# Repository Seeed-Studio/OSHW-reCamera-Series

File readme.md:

# Seeed Studio reCamera Hardware

English | [简体中文](README-CN.md)

This repository is the hardware documentation and design-resource hub for the
Seeed Studio reCamera product matrix:

- **reCamera 2002 / 2002w** (SG2002), a modular platform.
- **reCamera Pro** (RV1126B), a higher-performance integrated platform.

reCamera 2002 / 2002w and reCamera Pro are concurrently sold product families
for different application and performance requirements. This repository does
not describe them as replacement generations.

## Product matrix

| | reCamera 2002 / 2002w | reCamera Pro |
| --- | --- | --- |
| Processor | Sophgo SG2002 | Rockchip RV1126B |
| CPU | Dual C906 RISC-V cores | Quad-core Cortex-A53 at 1.2GHz |
| AI acceleration | 1 TOPS INT8 | 3 TOPS NPU |
| Memory | 256MB | 2GB / 4GB LPDDR4 |
| Standard camera | OV5647, 5MP | SC850SL, 8MP, 4K at 30fps |
| Hardware model | Interchangeable core, sensor, and base boards | Integrated camera with expansion interfaces |
| Documentation | [reCamera 2002 hardware](hardware/recamera-2002/) | [reCamera Pro hardware](hardware/recamera-pro/) |

### reCamera 2002 / 2002w

| Standard reCamera 2002 | reCamera 2002 HQ PoE | reCamera Gimbal 2002w |
| --- | --- | --- |
|  |  |  |
| Fixed camera; B101 base | GC2053 sensor; Ethernet and PoE | Two-axis brushless gimbal; B401 CAN base |

The repository contains editable KiCad sources, schematic PDFs, mechanical
files, and revision notes for the C1 core, S-series sensor boards, B-series base
boards, and Gimbal mechanical/power hardware. See the
[reCamera 2002 / 2002w product index](hardware/recamera-2002/products/).

### reCamera Pro

[Buy reCamera Pro 2GB from Seeed Studio](https://www.seeedstudio.com/reCamera-Pro-2GB.html)

The repository currently provides an official-specification snapshot, polished
storefront product images, and technical interface images for reCamera Pro. Editable Pro PCB and
mechanical source files should be added only when an approved hardware release
is available.

## Repository layout

```text
.
|-- hardware/
|   |-- recamera-2002/       # reCamera 2002 family board and mechanical sources
|   `-- recamera-pro/        # reCamera Pro family specifications and images
|-- docs/                    # Official sources and maintenance policy
|-- .github/workflows/       # Repository administration
|-- CONTRIBUTING.md
`-- LICENSE
```

## Scope

This is a **pure hardware repository**. 
If you need to access software-related repositories, please visit the official website.
[reCamera document](https://wiki.seeedstudio.com/recamera/)Obtain these resources from the Seeed Studio software repository.

Gimbal and HQ PoE are product forms within the reCamera 2002 family. Their
product-specific hardware is documented under `hardware/recamera-2002/products/`
and linked to shared boards.

## Source of truth

Hardware summaries are reviewed against official Seeed Studio product and Wiki
pages. See [docs/OFFICIAL_SOURCES.md](docs/OFFICIAL_SOURCES.md) for the source
list and review date. A currently shipped product page takes precedence over a
repository snapshot when specifications or available configurations change.

Contributions must follow [CONTRIBUTING.md](CONTRIBUTING.md). Unless a file says
otherwise, repository content is provided under the [Apache License 2.0](LICENSE).

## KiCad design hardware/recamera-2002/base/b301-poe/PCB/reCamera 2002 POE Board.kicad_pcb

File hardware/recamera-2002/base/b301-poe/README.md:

# B301 PoE base-board reference design

B301 adds Ethernet data and PoE-powered operation for an SG2002 reCamera. The
files here are an open-hardware **reference design** and must not be assumed to
be electrically or mechanically identical to every shipped reCamera HQ PoE
revision.

Editable KiCad sources are in [PCB](PCB/), enclosure files are in
[3D_Printed_Case](3D_Printed_Case/), and design images are in [static](static/).

> [!CAUTION]
> PoE input design involves safety, thermal, isolation, surge, and compliance
> requirements. Review the actual PSE/PD class, component ratings, isolation
> boundaries, heat dissipation, and IEEE 802.3 requirements before building.
> The powered reCamera endpoint is the **PD**; do not describe it as a PSE.

For a commercial reCamera HQ PoE product, follow its dedicated
[official quick-start guide](https://wiki.seeedstudio.com/recamera_hq_poe_getting_started/).

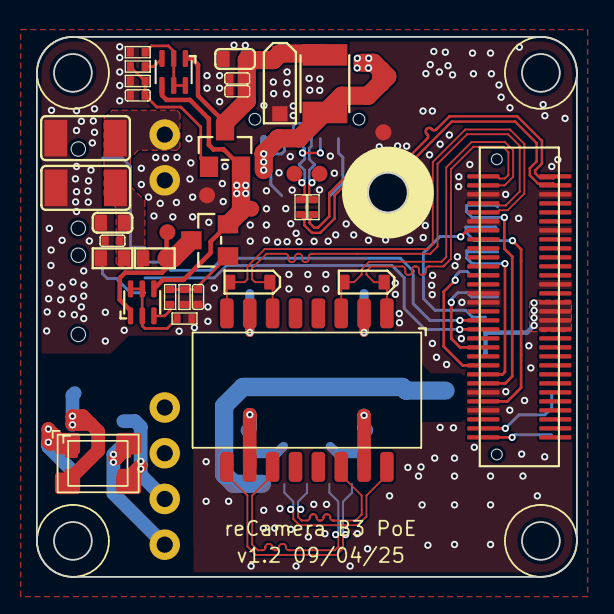
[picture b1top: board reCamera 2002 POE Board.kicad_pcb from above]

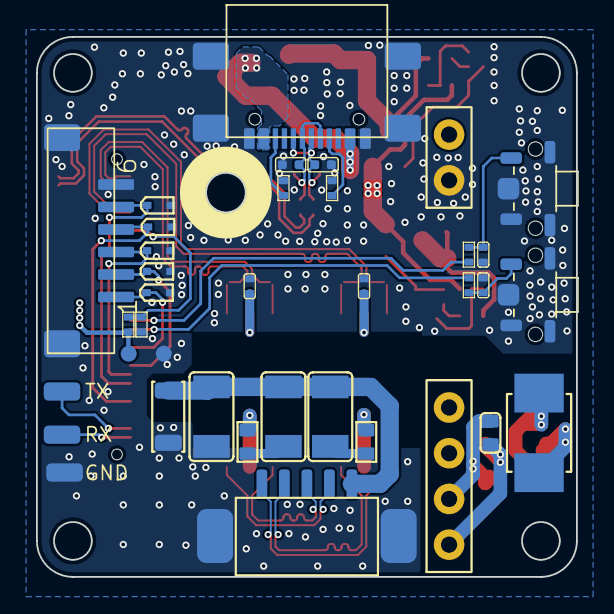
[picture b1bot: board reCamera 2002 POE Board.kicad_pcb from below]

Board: 4 copper layers, 30.0 x 30.0 mm, 75 parts (37 on the bottom side), 47 nets.

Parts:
C2: 100uF; C1206
C3, C4, C7, C13: 100nF; C0402
C5, C10, C17: 1nF; C1206
C6, C16: 10uF; C0603
C9, C18: 10pF; C0402
C11: 100pF; C0402
C12: 47uF; C1206
C19: 10nF; C0603
C49, C50: 10nF; C0402
D1: SMF5.0CA; SOD-123
D2, D3: ESDPSA0402V05; ESD-0402
D4: 58V 600W; DO-214AA-SMB-NONPOLAR
D5, D6, D7, D8, D13: CESD3V3D5; SOD-523
D11, D12: UDD32C03L01; SOD-323
F1: 2A; F1210
FB1: 120R; L0603
J1: ST-BTB-058060-A; BTB60-Male-Female-0.5-17.7x4.4mm
J2: ST-FH-254-0106-1*2P-PC3.0; JST2P-2.54-5.58X2.5X3.5MM
J3: 1.25-5A-WT; JST5_2P_1d25_7_9x4_3x3_4mm
J4: ST-FH-254-0106-1*4P-PC3.0; JST4P-2.54-10.66X2.5X3.5MM
J5: 1.25-6A-LT; FPC6-1.25-12.5X3.7X4.65MM
K1, K2: TD-1100AP-A4N-D1R; SW5-SMD-4.56X2.3X1.9MM
L1: CMC4532H-102-2P-T; INT4-2.2-4.5X3.2X2.8MM
L3: 300mA; INT4-1.45-3.3X2.5X2.5MM
Q1, Q2: CJ3407; SOT23
R2, R34, R39, R40: 100K; R0402
R4: 10K; R0402
R5: 20K; R0402
R6: 1M; R1206
R7, R12: 5.1K; R0402
R8, R9, R16, R17: 0R; R0402
R13, R14: 75R; R0603
R18: 1K; R0603
R41, R43: 100R; R0402
T1: KHX1631SR; TRF_16p_1d27_12d7x7d15x5d1mm
TP1, TP2, TP3: Test Point; TP-80X40MIL
TP4, TP5, TP6, TP8, TP9, TP10, TP11, TP12, TP15: Test Point; TP-D35MIL
U9, U10: BC856S; SOT-363
USB1: ST-USB-Y3120; USB2.0-TYPE-C-SMD-12X7.35X3.3MM

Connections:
+5V: F1.2, TP8.1 (T), USB1.A4_B9 (A4/B9/VBUS), USB1.B4_A9 (B4/A9/VBUS)
/POE Board/DN: D2.1, R9.1, TP4.1 (T), USB1.A7 (A7/DN1), USB1.B7 (B7/DN2)
/POE Board/DP: D3.1, R8.1, TP5.1 (T), USB1.A6 (A6/DP1), USB1.B6 (B6/DP2)
/POE Board/PHYRXN: J3.1, T1.9
/POE Board/PHYRXP: J3.2, T1.11
/POE Board/PHYTXN: J3.3, T1.14
/POE Board/PHYTXP: J3.4, T1.16
/POE Board/POE_VIN+_ModeA: D4.2, L1.1, L3.1, R14.2, T1.15
/POE Board/POE_VIN-_ModeA: D4.1, L1.4, L3.2, R13.2, T1.10
DEBUG_UART0_RX: J1.60, TP2.1 (T)
DEBUG_UART0_TX: J1.58, TP1.1 (T)
EPHY_RXN: D12.1, J1.10, T1.8
EPHY_RXP: D12.2, J1.8, T1.6
EPHY_TXN: D11.1, J1.4, T1.3
EPHY_TXP: D11.2, J1.2, T1.1
GND: C2.2, C3.1, C4.1, C6.2, C7.2, C9.2, C10.1, C11.2, C12.2, C13.2, C16.2, C18.2, C49.2, C50.2, D1.1, D2.2, D3.2, D5.1 (+), D6.1 (+), D7.1 (+), D8.1 (+), D13.1 (+), J1.5, J1.6, J1.12, J1.13, J1.25, J1.28, J1.30, J1.50, J1.54, J2.1, J3.6, J3.7, J5.6, J5.7, J5.8, K1.2, K1.S1, K1.S2, K1.S3, K2.2, K2.S1, K2.S2, K2.S3, R2.1, R4.1, R6.2, R7.1, R12.2, R18.1, R34.1, R39.1, R40.1, TP3.1 (T), TP6.1 (T), TP11.1 (T), TP12.1 (T), USB1.A1_B12 (A1/B12/GND), USB1.B1_A12 (B1/A12/GND), USB1.S1, USB1.S2, USB1.S3, USB1.S4
GNDPWR: C5.2, C10.2, C17.2, J3.5, R6.1
unnamed: C3.2, T1.2
unnamed: C4.2, T1.7
unnamed: C5.1, R13.1
unnamed: C9.1, K2.1, R16.2
unnamed: C2.1, C12.1, C13.1, C16.1, FB1.2, J2.2, R18.2
unnamed: C17.1, R14.1
unnamed: C18.1, K1.1, R17.2
unnamed: C19.1, J4.1, L1.2, L3.4
unnamed: C19.2, J4.2, L1.3, L3.3
unnamed: C50.1, Q1.1 (G), R39.2, R43.1
unnamed: C49.1, Q2.1 (G), R2.2, R41.1
unnamed: R34.2, U9.2, U9.5, U9.6
unnamed: R40.2, U10.2, U10.5, U10.6
unnamed: R41.2, U9.3
unnamed: R43.2, U10.3
unnamed: R12.1, USB1.A5 (A5/CC1)
unnamed: R7.2, USB1.B5 (B5/CC2)
POE_VOUT_5V: FB1.1, Q2.3 (D), TP10.1 (T), U9.1
SDIO_CLK/3V3: D5.2 (-), J1.52, J5.4
SDIO_CMD/3V3: D13.2 (-), J1.48, J5.5
SDIO_D0/3V3: D6.2 (-), J1.46, J5.3
SDIO_D1/3V3: D7.2 (-), J1.44, J5.2
SDIO_D3/3V3: D8.2 (-), J1.40, J5.1
UPGRAD_KEY: J1.36, R16.1
USB_DET: J1.14, R4.2, R5.1
USB_DN: J1.1, R9.2
USB_DP: J1.3, R8.2
VIN: J1.29, J1.31, J1.33, J1.35, Q1.2 (S), Q2.2 (S), R5.2, TP9.1 (T), TP15.1 (T), U9.4, U10.4
VIN_5V: C6.1, C7.1, C11.1, D1.2, F1.1, Q1.3 (D), U10.1
nRESET: J1.34, R17.1

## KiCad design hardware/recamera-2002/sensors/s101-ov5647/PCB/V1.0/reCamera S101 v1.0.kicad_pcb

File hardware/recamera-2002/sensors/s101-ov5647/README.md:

# S101 OV5647 sensor board

S101 is the default sensor board shipped with standard reCamera 2002/2002w
Basic products.

| Item | Value |
| --- | --- |
| Sensor | OV5647, rolling shutter |
| Resolution | 5MP (2592 × 1944) |
| Optical format | 1/4 inch |
| Pixel size | 1.4µm |
| Aperture | F2.8 |
| Focal length | 3.46mm |
| Field of view | 65° |
| Output | RAW10 |

The board also carries the reCamera's microphone, external-speaker connection,
four fill LEDs, and status/programmable LEDs.

## Resources

- Editable KiCad sources: [PCB](PCB/)
- [Schematic PDF](static/reCamera%20S101%20v1.1_SCH_PDF_240927.pdf)
- Enclosure files: [3D_Printed_Case](3D_Printed_Case/)

The repository includes more than one PCB revision. Use the revision matching
the physical board and validate it before manufacture.

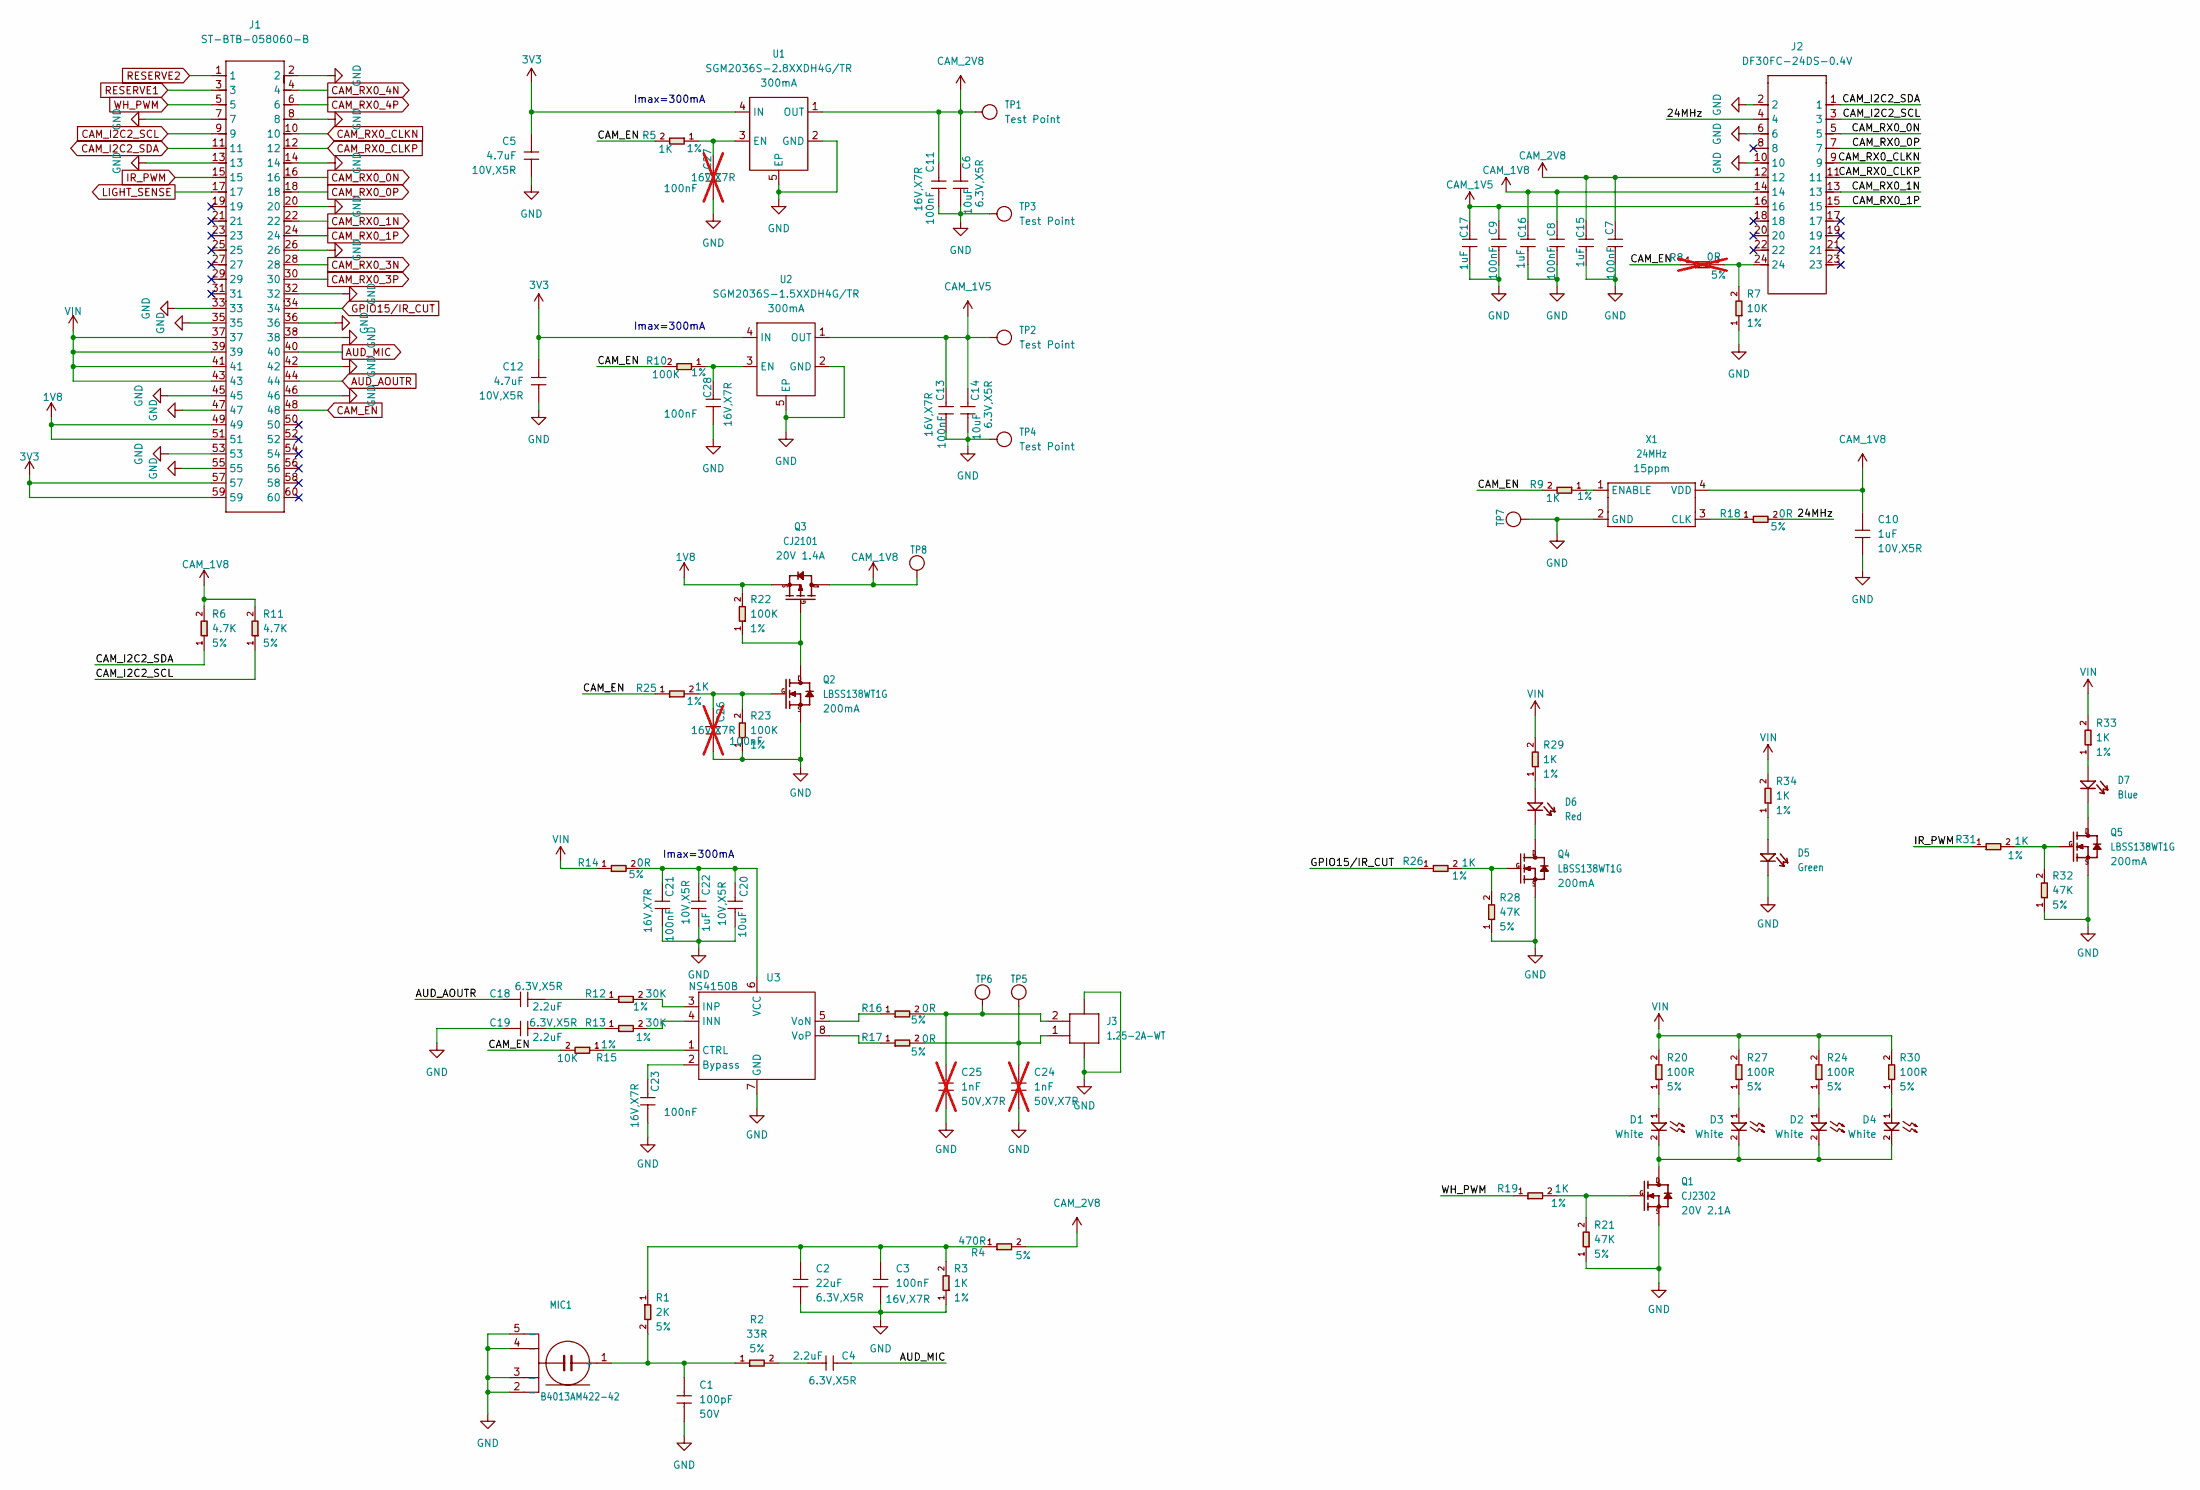
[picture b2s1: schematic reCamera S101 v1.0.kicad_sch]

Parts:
C1: 100pF; C0402; Voltage Rating 50V; MPN CC0402JRNPO9BN101
C2: 22uF; C0603; Voltage Rating 6.3V,X5R; MPN CC0603MRX5R5BB226
C3, C7, C8, C9, C11, C13, C21, C23, C28: 100nF; C0402; Voltage Rating 16V,X7R; MPN CC0402KRX7R7BB104
C4, C18, C19: 2.2uF; C0402; Voltage Rating 6.3V,X5R; MPN CC0402MRX5R5BB225
C5, C12: 4.7uF; C0603; Voltage Rating 10V,X5R; MPN CC0603KRX5R6BB475
C6, C14: 10uF; C0402; Voltage Rating 6.3V,X5R; MPN CC0402MRX5R5BB106
C10, C15, C16, C17, C22: 1uF; C0402; Voltage Rating 10V,X5R; MPN CC0402KRX5R6BB105
C20: 10uF; C0603; Voltage Rating 10V,X5R; MPN CC0603KRX5R6BB106
C24, C25: 1nF; C0402; Voltage Rating 50V,X7R; MPN CC0402KRX7R9BB102; not fitted
C26, C27: 100nF; C0402; Voltage Rating 16V,X7R; MPN CC0402KRX7R7BB104; not fitted
D1, D2, D3, D4: White; LED2-2.54-4.15MM; MPN 204-15UTC/S400-X9
D5: Green; LED-0402; MPN BL-HGE37A-AV-TRB
D6: Red; LED-0402; MPN BL-HUB37A-AV-TRB
D7: Blue; LED-0402; MPN BL-HB337A-AV-TRB
J1: ST-BTB-058060-B; BTB60-Male-Female-0.5-17.7x4.4mm; MPN ST-BTB-058060-B
J2: DF30FC-24DS-0.4V; BTB2x12P_0d4_7_02x3_76x0_9mm; MPN DF30FC-24DS-0.4V
J3: 1.25-2A-WT; GH2-1.25-7.4X5.3X3.5MM; MPN 1.25-2A-WT
MIC1: B4013AM422-42; MIC-5P-SMD-4X4MM; MPN B4013AM422-42
Q1: CJ2302; SOT23; Rating 20V 2.1A; MPN CJ2302
Q2, Q4, Q5: LBSS138WT1G; SOT-323; Rating 200mA; MPN LBSS138WT1G
Q3: CJ2101; SOT-323; Rating 20V 1.4A; MPN CJ2101
R1: 2K; R0402; Power Rating 5%; MPN RC0402JR-072KL
R2: 33R; R0402; Power Rating 5%; MPN RC0402JR-0733RL
R3, R5, R9, R19, R25, R26, R29, R31, R33, R34: 1K; R0402; Power Rating 1%; MPN RC0402FR-071KL
R4: 470R; R0402; Power Rating 5%; MPN RC0402JR-07470RL
R6, R11: 4.7K; R0402; Power Rating 5%; MPN RC0402JR-074K7L
R7, R15: 10K; R0402; Power Rating 1%; MPN RC0402FR-0710KL
R8: 0R; R0402; Power Rating 5%; MPN RC0402JR-070RL; not fitted
R10, R22, R23: 100K; R0402; Power Rating 1%; MPN RC0402FR-07100KL
R12, R13: 30K; R0402; Power Rating 1%; MPN RC0402FR-0730KL
R14, R16, R17, R18: 0R; R0402; Power Rating 5%; MPN RC0402JR-070RL
R20, R24, R27, R30: 100R; R0603; Power Rating 5%; MPN RC0603JR-07100RL
R21, R28, R32: 47K; R0402; Power Rating 5%; MPN RC0402JR-0747KL
TP1, TP2, TP3, TP4, TP5, TP6, TP7, TP8: Test Point; TP-D35MIL; Part Type Test Point
U1: SGM2036S-2.8XXDH4G/TR; X2SON4-0.625-1x1x0.6mm; Rating 300mA; MPN SGM2036S-2.8XXDH4G/TR
U2: SGM2036S-1.5XXDH4G/TR; X2SON4-0.625-1x1x0.6mm; Rating 300mA; MPN SGM2036S-1.5XXDH4G/TR
U3: NS4150B; MSOP8-0.65-3X3X1MM; MPN NS4150B
X1: 24MHz; X4-SMD-2.0X1.6MM; Rating 15ppm; MPN 9C24000004

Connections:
1V8: J1.49, J1.51, Q3.2 (S), R22.2
3V3: C5.1, C12.1, J1.57, J1.59, U1.4 (IN), U2.4 (IN)
/24MHz: J2.4, R18.2
AUD_AOUTR: C18.1, J1.44
AUD_MIC: C4.1, J1.40
CAM_1V5: C9.1, C13.1, C14.1, C17.1, J2.16, TP2.1 (T), U2.1 (OUT)
CAM_1V8: C8.1, C10.1, C16.1, J2.14, Q3.3 (D), R6.2, R11.2, TP8.1 (T), X1.4 (VDD)
CAM_2V8: C6.1, C7.1, C11.1, C15.1, J2.12, R4.2, TP1.1 (T), U1.1 (OUT)
CAM_EN: J1.48, R5.2, R8.1, R9.2, R10.2, R15.2, R25.1
CAM_I2C2_SCL: J1.9, J2.3, R11.1
CAM_I2C2_SDA: J1.11, J2.1, R6.1
CAM_RX0_0N: J1.16, J2.5
CAM_RX0_0P: J1.18, J2.7
CAM_RX0_1N: J1.22, J2.13
CAM_RX0_1P: J1.24, J2.15
CAM_RX0_3N: J1.28
CAM_RX0_3P: J1.30
CAM_RX0_4N: J1.4
CAM_RX0_4P: J1.6
CAM_RX0_CLKN: J1.10, J2.9
CAM_RX0_CLKP: J1.12, J2.11
GND: C1.2, C2.2, C3.2, C5.2, C6.2, C7.2, C8.2, C9.2, C10.2, C11.2, C12.2, C13.2, C14.2, C15.2, C16.2, C17.2, C19.1, C20.2, C21.2, C22.2, C23.2, C24.2, C25.2, C26.2, C27.2, C28.2, D5.2 (-), J1.2, J1.7, J1.8, J1.13, J1.14, J1.20, J1.26, J1.32, J1.33, J1.35, J1.36, J1.38, J1.42, J1.45, J1.46, J1.47, J1.53, J1.55, J2.2, J2.6, J2.10, J3.3, J3.4, MIC1.2 (-), MIC1.3 (-), MIC1.4 (-), MIC1.5 (-), Q1.2 (S), Q2.2 (S), Q4.2 (S), Q5.2 (S), R3.1, R7.1, R21.1, R23.1, R28.1, R32.1, TP3.1 (T), TP4.1 (T), TP7.1 (T), U1.2 (GND), U1.5 (EP), U2.2 (GND), U2.5 (EP), U3.7 (GND), X1.2 (GND)
GPIO15/IR_CUT: J1.34, R26.1
IR_PWM: J1.15, R31.1
LIGHT_SENSE: J1.17
unnamed: C2.1, C3.1, R1.1, R3.2, R4.1
unnamed: C4.2, R2.2
unnamed: C18.2, R12.1
unnamed: C19.2, R13.1
unnamed: D1.1, R20.1
unnamed: D2.1, R24.1
unnamed: D3.1, R27.1
unnamed: D4.1, R30.1
unnamed: D5.1 (+), R34.1
unnamed: D6.1 (+), R29.1
unnamed: D6.2 (-), Q4.3 (D)
unnamed: D7.1 (+), R33.1
unnamed: D7.2 (-), Q5.3 (D)
unnamed: J2.24, R7.2, R8.2
unnamed: C1.1, MIC1.1 (+), R1.2, R2.1
unnamed: D1.2, D2.2, D3.2, D4.2, Q1.3 (D)
unnamed: Q1.1 (G), R19.2, R21.2
unnamed: Q2.3 (D), Q3.1 (G), R22.1
unnamed: C26.1, Q2.1 (G), R23.2, R25.2
unnamed: Q4.1 (G), R26.2, R28.2
unnamed: Q5.1 (G), R31.2, R32.2
unnamed: C24.1, J3.1, R17.2, TP5.1 (T)
unnamed: C25.1, J3.2, R16.2, TP6.1 (T)
unnamed: C27.1, R5.1, U1.3 (EN)
unnamed: C28.1, R10.1, U2.3 (EN)
unnamed: C23.1, U3.2 (Bypass)
unnamed: R15.1, U3.1 (CTRL)
unnamed: R13.2, U3.4 (INN)
unnamed: R12.2, U3.3 (INP)
unnamed: C20.1, C21.1, C22.1, R14.2, U3.6 (VCC)
unnamed: R16.1, U3.5 (VoN)
unnamed: R17.1, U3.8 (VoP)
unnamed: R18.1, X1.3 (CLK)
unnamed: R9.1, X1.1 (ENABLE)
RESERVE1: J1.3
RESERVE2: J1.1
VIN: J1.37, J1.39, J1.41, J1.43, R14.1, R20.2, R24.2, R27.2, R29.2, R30.2, R33.2, R34.2
WH_PWM: J1.5, R19.1

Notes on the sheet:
Imax=300mA

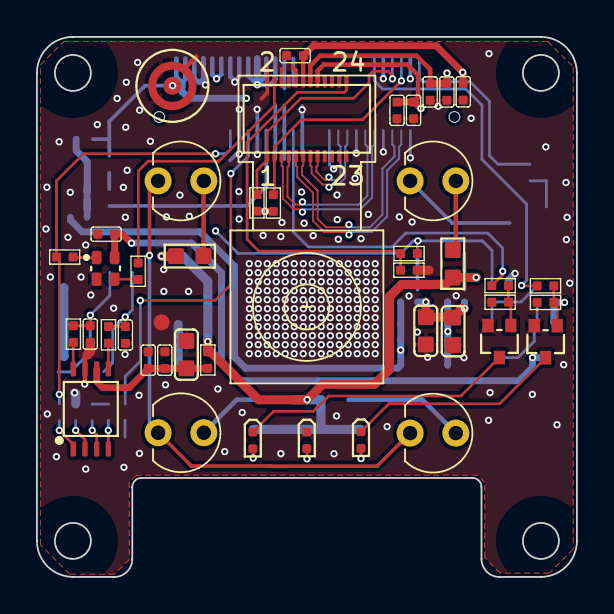
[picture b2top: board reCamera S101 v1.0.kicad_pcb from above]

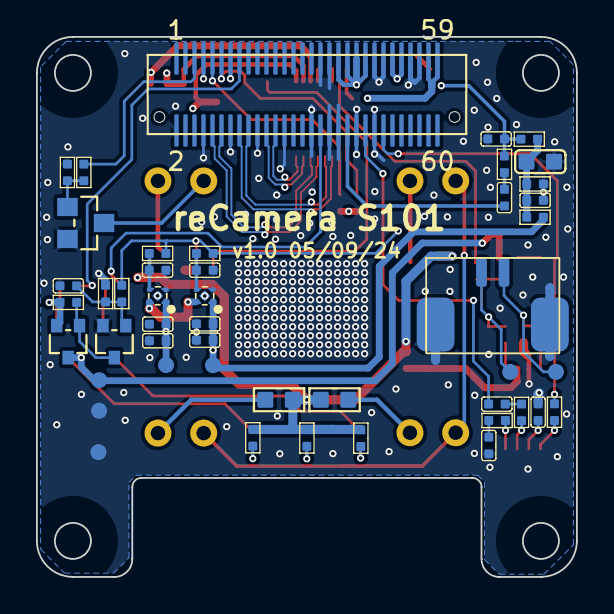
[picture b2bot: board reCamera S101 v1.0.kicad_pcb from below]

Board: 4 copper layers, 30.0 x 30.0 mm, 90 parts (47 on the bottom side), 56 nets.

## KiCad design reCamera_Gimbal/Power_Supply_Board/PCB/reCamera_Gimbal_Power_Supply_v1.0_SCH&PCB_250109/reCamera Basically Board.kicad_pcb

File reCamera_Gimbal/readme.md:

# 🎨 reCamera Gimbal Programmable Development Kit 

## 🔥Introduction
Welcome to the reCamera Gimbal Programmable Development Kit. This kit provides resources and tools for developers to control and customize the reCamera Gimbal. It includes sample code for debugging gimbal motor operations and status outputs, offering program entry points to drive the gimbal motor using CAN for precise control and functionality.

## Table of Contents

- [🔩 Pre-requisite](#-pre-requisite)
- [🪢 Gimbal Dashboard Preview with Node-RED ](#-gimbal-dashboard-preview-with-node-red)
- [⚙️ Hardware Overview](#-hardware-overview)
- [💡 Custom Development](#-custom-development)
- [🔥 Gimbal STP](#-gimbal-stp)
- [📀 Flash motors firmware](#-flash-motors-firmware)

## 🔩 Pre-requisite
- reCamera OS 0.2.0
- 12V 2A power supply
- USB Type-C cable

## 🪢 Gimbal Dashboard Preview with Node-RED

Gimbal Node-REd Dashboard includes camera preview, model confidence/IoU Settings, gimbal manual control, object auto-tracking and shortcut buttons such as sleep, standby, calibration and Emergency Stop. The PID settings are also included for fine-tuning as each device is self-assembled.

You can see how to deploy json flow on Node-RED [here](https://github.com/jby5122/OSHW-reCamera-Series/tree/main/Node-RED_Flow#%EF%B8%8F-how-to-deploy-dashboard-flow). 

- View [Gimbal Dashboard V1.0.json](./src/Dashboard/Gimbal_DashboardV1.0.json) (PID settings are also included)
- View [Motor_PID_Config.json](./src/Dashboard/Motor_PID_Config.json) (Individual PID settings for each motor in case you want to add this to your own flow)

## Hardware Overview

To enable the reCamera to drive the gimbal motor, the reCamera's base board needs to be replaced to [B4_CAN](https://github.com/Seeed-Studio/OSHW-reCamera-Series/tree/main/reCamera_Base_Board/B4_CAN) to enable CAN communication.

Up             |  Bottom
:-------------------------:|:-------------------------:
  |  

You can use the Debugging Port connections to control the motor and communicate with the reCamera via the upper monitor. Alternatively, you can control the motor directly through the reCamera.

| **Processing System**                |                                                         |                                                         |
| ------------------------------------ | ------------------------------------------------------- | ------------------------------------------------------- |
| SOC                                  | SG2002                                                  |                                                         |
| CPU                                  | C906@1GHZ + C906@700MHz                                 |                                                         |
| AI Performance                       | 1 Tops @ Int8                                           |                                                         |
| MCU                                  | 8051 @ 8KB SRAM                                         |                                                         |
| Operating System                     | Linux                                                   |                                                         |
| Memory                               | 256 MB                                                  |                                                         |
| Video Encoder                        | 5MP @ 30Fps                                             |                                                         |
| **Basic**                            |                                                         |                                                         |
| Camera Sensor                        | OV5647                                                  |                                                         |
| eMMC                                 | 8GB / 64GB                                              |                                                         |
| Power Supply                         | 12-24V DC Jack to XT30 connector                        |                                                         |
| Power Consumption(static)            | 12V,185mA; 24V,150mA                                    |                                                         |
| **Interface**                        |                                                         |                                                         |
| USB                                  | USB 2.0 Type-C                                          |                                                         |
| Wireless                             | Wi-Fi 2.4G/5G Bluetooth 4.2/5.0                         |                                                         |
| Button                               | 1 x Reboot Button, 1 x User Button                      |                                                         |
| Fill LEDs                            | 4 x 0.3w White Light                                    |                                                         |
| LED                                  | 1 x Power Indicator, 2 x IO programmable indicator      |                                                         |
| Mic                                  | On-Board Mic                                            |                                                         |
| Speaker                              | External Speaker                                        |                                                         |
| **Motor Spec**                       | MS3008                                                  | MS3506                                                  |
| Turns                                | 54                                                      | 60                                                      |
| Rated Voltage(V)                     | 12                                                      | 12                                                      |
| Max Speed(rpm)                       | 2000                                                    | 2100                                                    |
| Rated Torque(N.m)                    | 0.04                                                    | 0.05                                                    |
| Rated Speed(rpm)                     | 1160                                                    | 1250                                                    |
| Rated Current(A)                     | 0.64                                                    | 0.79                                                    |
| Max Power(W)                         | 4.6                                                     | 6.4                                                     |
| Motor Poles                          | 14                                                      | 14                                                      |
| Operating temperature (℃)            | -25~60                                                  | -25~60                                                  |
| Motor Weight(g)                      | 49                                                      | 63                                                      |
| Drive Input Voltage (V)              | 6~16                                                    | 6~16                                                    |
| Communication                        | CAN                                                     | CAN                                                     |
| Communication Frequency (Hz)         | CAN@1Mbps:2KHz                                          | CAN@1Mbps:2KHz                                          |
| Encoder                              | 15 bit Magnetic Encoder                                 | 15 bit Magnetic Encoder                                 |
| CAN Baut Rate                        | 100K、125K、250K、500K、1M                              | 100K、125K、250K、500K、1M                              |
| Control Mode                         | Open Loop(24KHz) /Speed Loop(4KHz) /Position Loop(2KHz) | Open Loop(24KHz) /Speed Loop(4KHz) /Position Loop(2KHz) |
| **Ambient Conditions**               |                                                         |                                                         |
| Operating Temperature                | -20～50 ℃                                               |                                                         |
| Operating Humidity                   | 0～90%                                                  |                                                         |
| **Others**                           |                                                         |                                                         |
| Heat Dissipation                     | Fanless                                                 |                                                         |
| Warranty                             | 1 years                                                 |                                                         |
| **Mechanical**                       |                                                         |                                                         |
| Finished ProductDimension(W x H x D) | 68x112x71mm                                             |                                                         |
| Enclosure                            | Polyamide(PA) Nylon                                     |                                                         |
| Weight(Net)                          | 230g                                                    |                                                         |

## 💡 Custom Development

First, you need to prepare a linux operating system to compile the program.
To compile a binary that can run on reCamera, [the cross-compiler tool](https://github.com/sophgo/host-tools/tree/bd66fcc8ed918eac4d6ac076ff8b1da7290b66cb) for riscv needs to be downloaded. 

### Cross-Compilation

Open a terminal in any directory on your Ubuntu system.
You can download host-tools by running this command on your linux system:

```bash
sudo apt install vim
sudo apt install git
git clone https://github.com/sophgo/host-tools.git
```

After the download is complete go to the file "/host-tools/gcc/riscv64-linux-musl-x86_64/bin"

Enter "pwd" to see the absolute path and copy it.

```
pwd
```

```
cd
vim .bashrc
```

Based on the previous “pwd” command, add the following to the end of the file 

```
export PATH=$PATH:/home/kong/Downloads/host-tools/gcc/riscv64-linux-musl-x86_64/bin
```

Click esc and type “:wq” to save the .bashrc.

```
source .bashrc
```

Go back to the OSHW-reCamera-Series/reCamera_Gimbal/src/send directory. Compile can_send.c and run it.

```
riscv64-unknown-linux-musl-gcc can_send.c -o can_send
```

Open a terminal in the directory where can_send is stored.

```
scp ./can_send root@192.168.42.1:~/
```

```
ssh root@192.168.42.1
```

```
touch Angle.txt 
./can_send

echo "1_90_90+2_90_90" >> Angle.txt
```

## 🔥 Gimbal STP

You can [download the STP file](./3D_Printed_Case) of this gimbal for 3D printing and assemble it. 

| Preview | Models |
| ------- | ------ |
|  | [Download](./3D_Printed_Case/recamera-yantai_arm_30.stp)       |
|  | [Download](./3D_Printed_Case/platform-box_29.stp)              |
|  | [Download](./3D_Printed_Case/bottom-plate_10.stp)              |
|  | [Download](./3D_Printed_Case/brushlessmotor-ms3506_4.stp)      |
|  | [Download](./3D_Printed_Case/brushlessmotor-ms3008v2_2.stp)    |
|  | [Download](./3D_Printed_Case/recamera-gimbalcover-4040_20.stp) |
|  | [Download](./3D_Printed_Case/can-case_3.stp)                   |
|  | [Download](./3D_Printed_Case/recamera-middleframe-4040-1_27.stp)|
|  | [Download](./3D_Printed_Case/recamera-sensorcover-4040-1_36.stp)|
|  | [Download](./3D_Printed_Case/glass-4040_6.stp)                 |

## 📀 Flash motors firmware

### Motor ID Set

ID changes can be made using MS_Motor/LK motor tool [V2.35.exe](MotorTools/CN/KY%20motor%20tool%20V2.35.exe). Connect the PC (Windows) to the USB-CAN module, with H, L, and GND of the USB-CAN module connected to H, L, and V- of the motor. Connect the positive and negative terminals of a 12V power supply to V+ and V- of the motor to enable parameter changes. For further instructions on using LK motor tool V2.35.exe, refer to MotorTools/EN/Upper_monitor_motor_debuging_instruction.pdf. 

Only two motors are used in this head, so it is sufficient to set the IDs of the two motors to 01 and 02 respectively.

### How to update motor firmware
WIP...

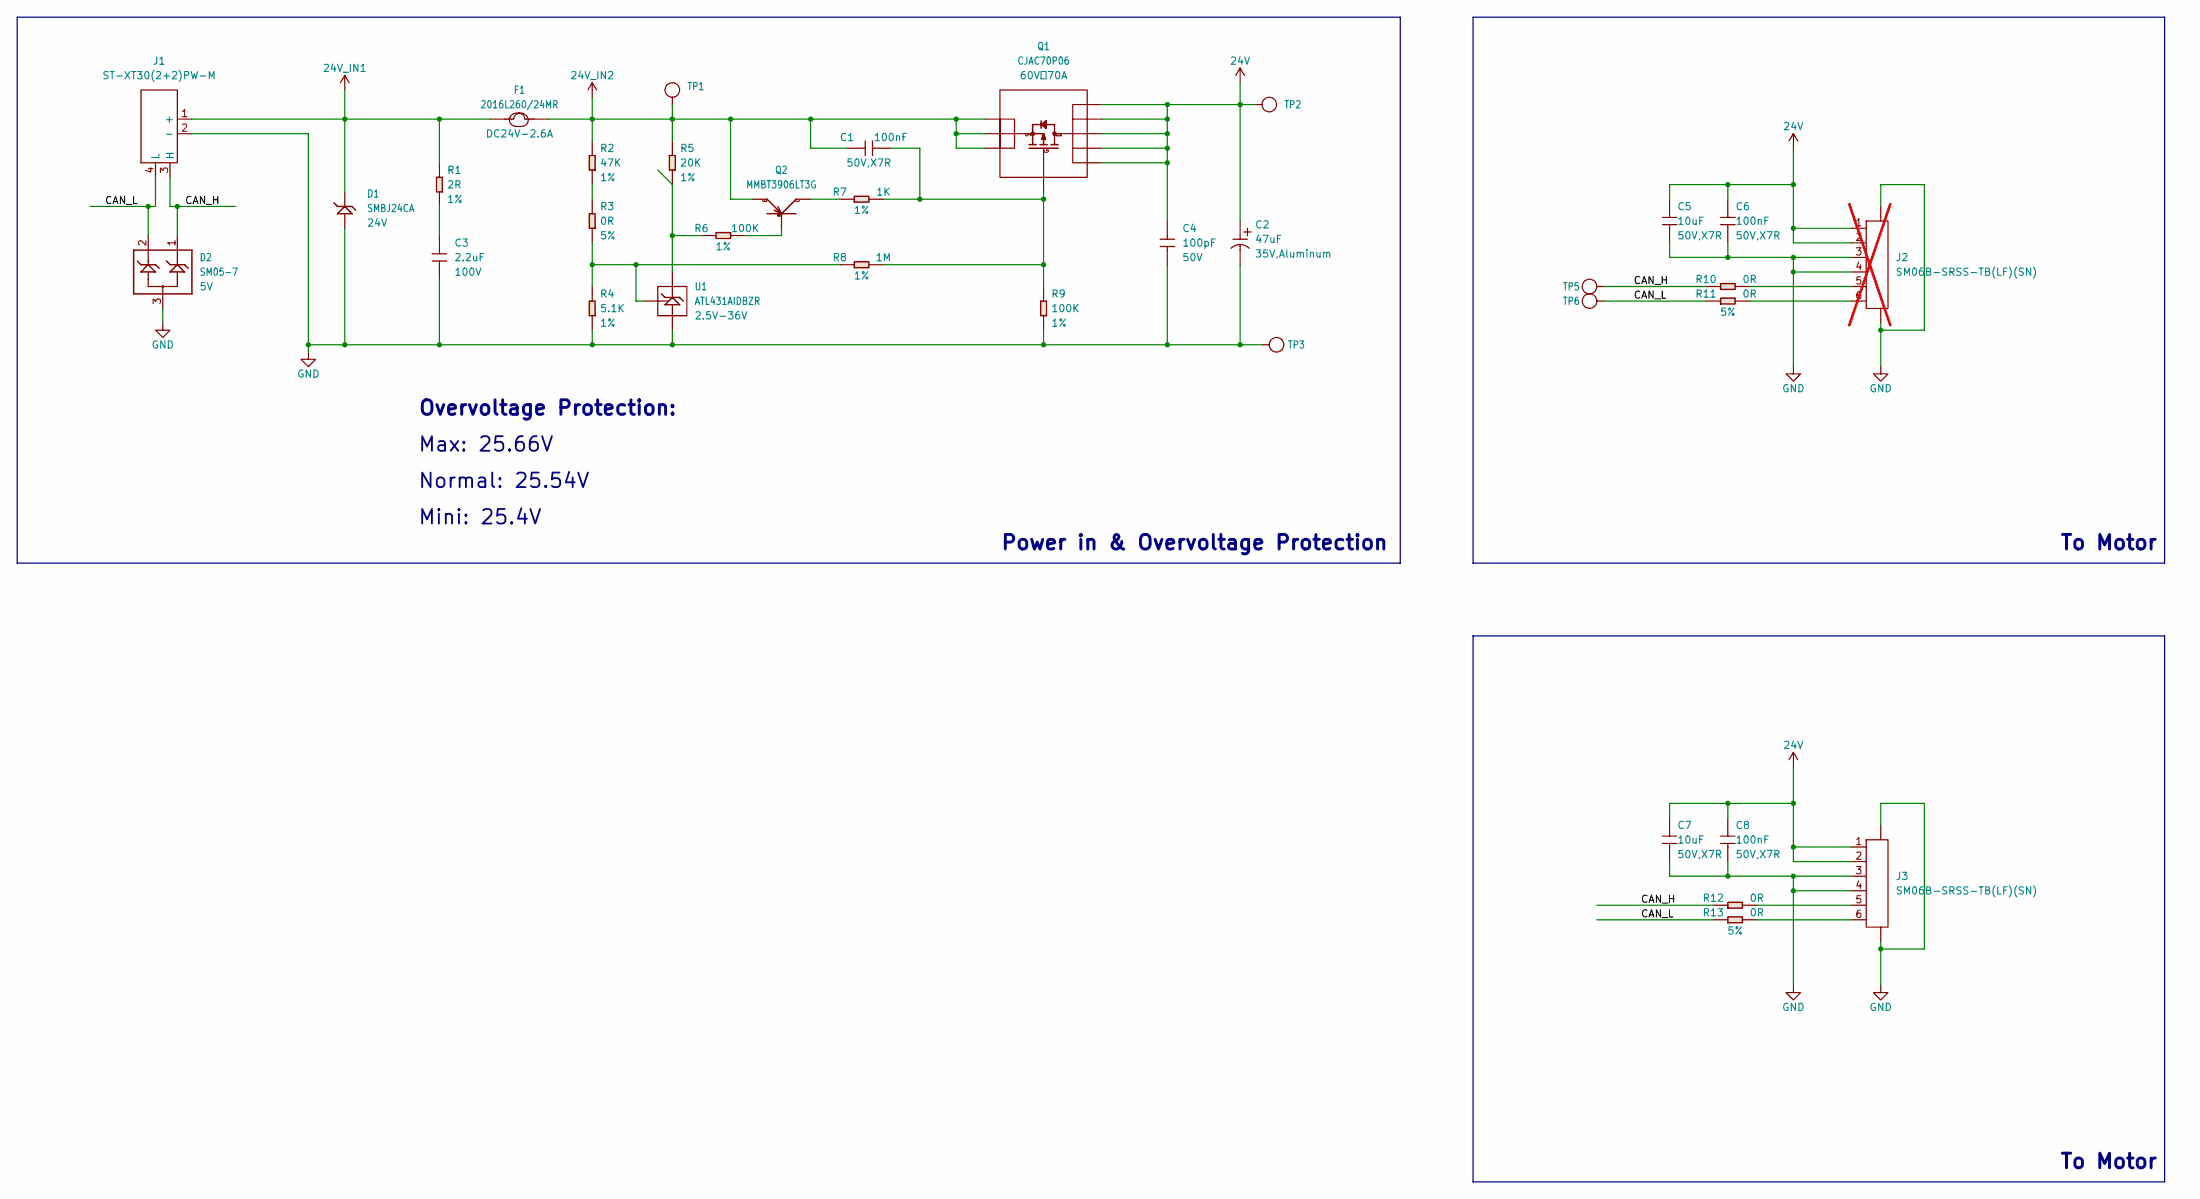
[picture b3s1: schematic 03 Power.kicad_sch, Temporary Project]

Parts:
C1, C6, C8: 100nF; C0603; Voltage Rating 50V,X7R; MPN CC0603KRX7R9BB104
C2: 47uF; ELECTRO-SMD-C-6MM; Voltage Rating 35V,Aluminum; MPN 35TZV47M6.3X6.1
C3: 2.2uF; C1210; Voltage Rating 100V; MPN CC1210KKX7R0BB225
C4: 100pF; C0402; Voltage Rating 50V; MPN CC0402JRNPO9BN101
C5, C7: 10uF; C1206; Voltage Rating 50V,X7R; MPN CL31B106KBHNNNE
D1: SMBJ24CA; DO-214AA_SMB; Rating 24V; MPN SMBJ24CA
D2: SM05-7; SOT-23; Rating 5V; MPN SM05-7
F1: 2016L260/24MR; F2016; Rating DC24V-2.6A; MPN 2016L260/24MR
J1: ST-XT30(2+2)PW-M; XT30-2+2P-15.5x12.5x5.2mm; MPN ST-XT30(2+2)PW-M
J2: SM06B-SRSS-TB(LF)(SN); SMD-SH1.0-6P-90D; MPN SM06B-SRSS-TB(LF)(SN); not fitted
J3: SM06B-SRSS-TB(LF)(SN); SMD-SH1.0-6P-90D; MPN SM06B-SRSS-TB(LF)(SN)
Q1: CJAC70P06; PG-TDSON-8-1.27-6X5X1MM; Rating 60V，70A; MPN CJAC70P06
Q2: MMBT3906LT3G; SOT-23; MPN MMBT3906LT3G
R1: 2R; R2512; Power Rating 1%; MPN RC2512FK-072RL
R2: 47K; R0402; Power Rating 1%; MPN RC0402FR-0747KL
R3, R10, R11, R12, R13: 0R; R0402; Power Rating 5%; MPN RC0402JR-070RL
R4: 5.1K; R0402; Power Rating 1%; MPN RC0402FR-075K1L
R5: 20K; R0402; Power Rating 1%; MPN RC0402FR-0720KL
R6, R9: 100K; R0402; Power Rating 1%; MPN RC0402FR-07100KL
R7: 1K; R0402; Power Rating 1%; MPN RC0402FR-071KL
R8: 1M; R0402; Power Rating 1%; MPN RC0402FR-071ML
TP1, TP2, TP3, TP5, TP6: Test Point; TP-1.6MM-ROUND; Part Type Test Point
U1: ATL431AIDBZR; SOT-23; Rating 2.5V-36V; MPN ATL431AIDBZR

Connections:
24V: C2.1, C4.1, C5.1, C6.1, C7.1, C8.1, J2.1, J2.2, J3.1, J3.2, Q1.5 (D1), Q1.6 (D2), Q1.7 (D3), Q1.8 (D4), Q1.9 (D5), TP2.1 (T)
24V_IN1: D1.2 (-), F1.1, J1.1 (+), R1.2
24V_IN2: C1.1, F1.2, Q1.1 (S1), Q1.2 (S2), Q1.3 (S3), Q2.2 (E), R2.2, R5.2, TP1.1 (T)
/03 Power/CAN_H: D2.1, J1.3 (H), R10.1, R12.1, TP5.1 (T)
/03 Power/CAN_L: D2.2, J1.4 (L), R11.1, R13.1, TP6.1 (T)
GND: C2.2, C3.2, C4.2, C5.2, C6.2, C7.2, C8.2, D1.1 (+), D2.3, J1.2 (-), J2.3, J2.4, J2.7, J2.8, J3.3, J3.4, J3.7, J3.8, R4.1, R9.1, TP3.1 (T), U1.3 (+)
unnamed: C3.1, R1.1
unnamed: J2.5, R10.2
unnamed: J2.6, R11.2
unnamed: J3.5, R12.2
unnamed: J3.6, R13.2
unnamed: C1.2, Q1.4 (G), R7.2, R8.2, R9.2
unnamed: Q2.1 (B), R6.1
unnamed: Q2.3 (C), R7.1
unnamed: R2.1, R3.2
unnamed: R5.1, R6.2, U1.1 (-)
unnamed: R3.1, R4.2, R8.1, U1.2 (Vref)

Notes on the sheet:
To Motor
Normal: 25.54V
Max: 25.66V
Power in & Overvoltage Protection
Overvoltage Protection:
Mini: 25.4V

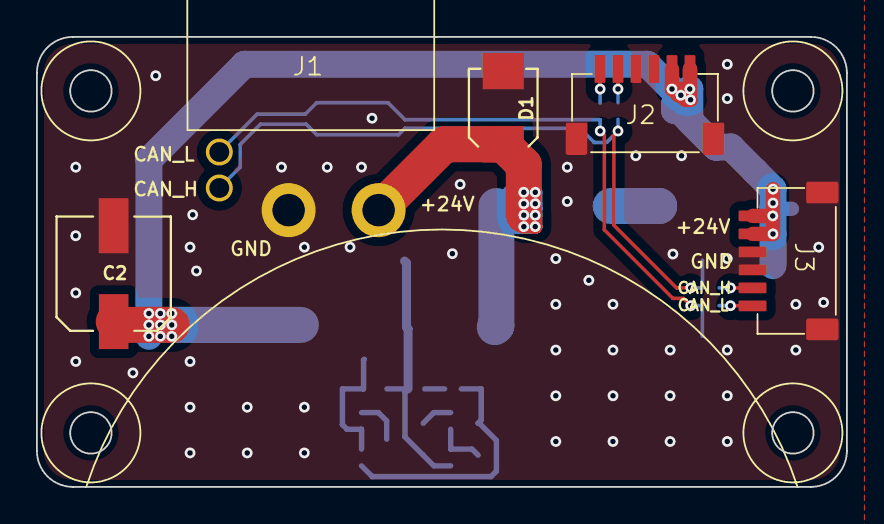
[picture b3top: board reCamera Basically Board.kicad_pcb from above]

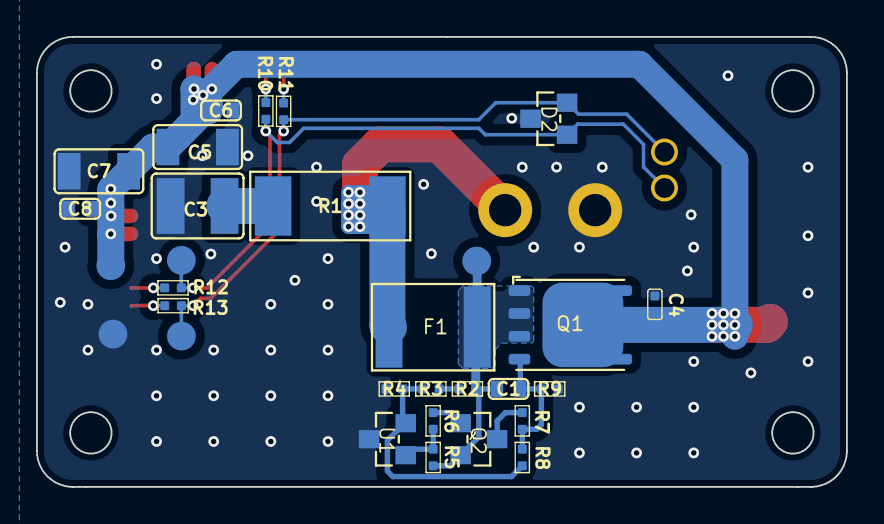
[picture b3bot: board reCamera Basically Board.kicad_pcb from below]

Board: 2 copper layers, 45.0 x 25.0 mm, 35 parts (30 on the bottom side), 17 nets.
